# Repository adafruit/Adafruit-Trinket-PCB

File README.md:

## Adafruit Trinket 3.3 and 5V Microcontroller PCBs
&nbsp; 
<br />
Click to purchase from the Adafruit Shop:
- [Adafruit Trinket - Mini Microcontroller - 3.3V Logic - MicroUSB](https://www.adafruit.com/product/1500)
- [Adafruit Trinket - Mini Microcontroller - 5V Logic - MicroUSB](https://www.adafruit.com/product/1501)

Deprecation Warning: The Trinket bit-bang USB technique it uses doesn't work as well as it did in 2014, many modern computers won't work well. So while we still carry the Trinket so that people can maintain some older projects, we no longer recommend it. Please check out the **Trinket M0**. It has built-in USB, more capabilities, and is comparable in price!

Trinket may be small, but do not be fooled by its size! It's a tiny microcontroller board, built around the Atmel ATtiny85, a little chip with a lot of power. We wanted to design a microcontroller board that was small enough to fit into any project, and low cost enough to use without hesitation. Perfect for when you don't want to give up your expensive dev-board and you aren't willing to take apart the project you worked so hard to design. It's our lowest-cost arduino-IDE programmable board!

This is the CAD & PCB data for the Adafruit Trinket 3V & 5V. The PCB format is EagleCAD schematic and board layout
- https://www.adafruit.com/products/1500
- https://www.adafruit.com/products/1501

### License

Adafruit invests time and resources providing this open source design, please support Adafruit and open-source hardware by [purchasing products from Adafruit](https://www.adafruit.com)!

All text above must be included in any redistribution

Designed by Limor Fried/Ladyada for Adafruit Industries.
Creative Commons Attribution/Share-Alike, all text above must be included in any redistribution. 
See license.txt for additional information.

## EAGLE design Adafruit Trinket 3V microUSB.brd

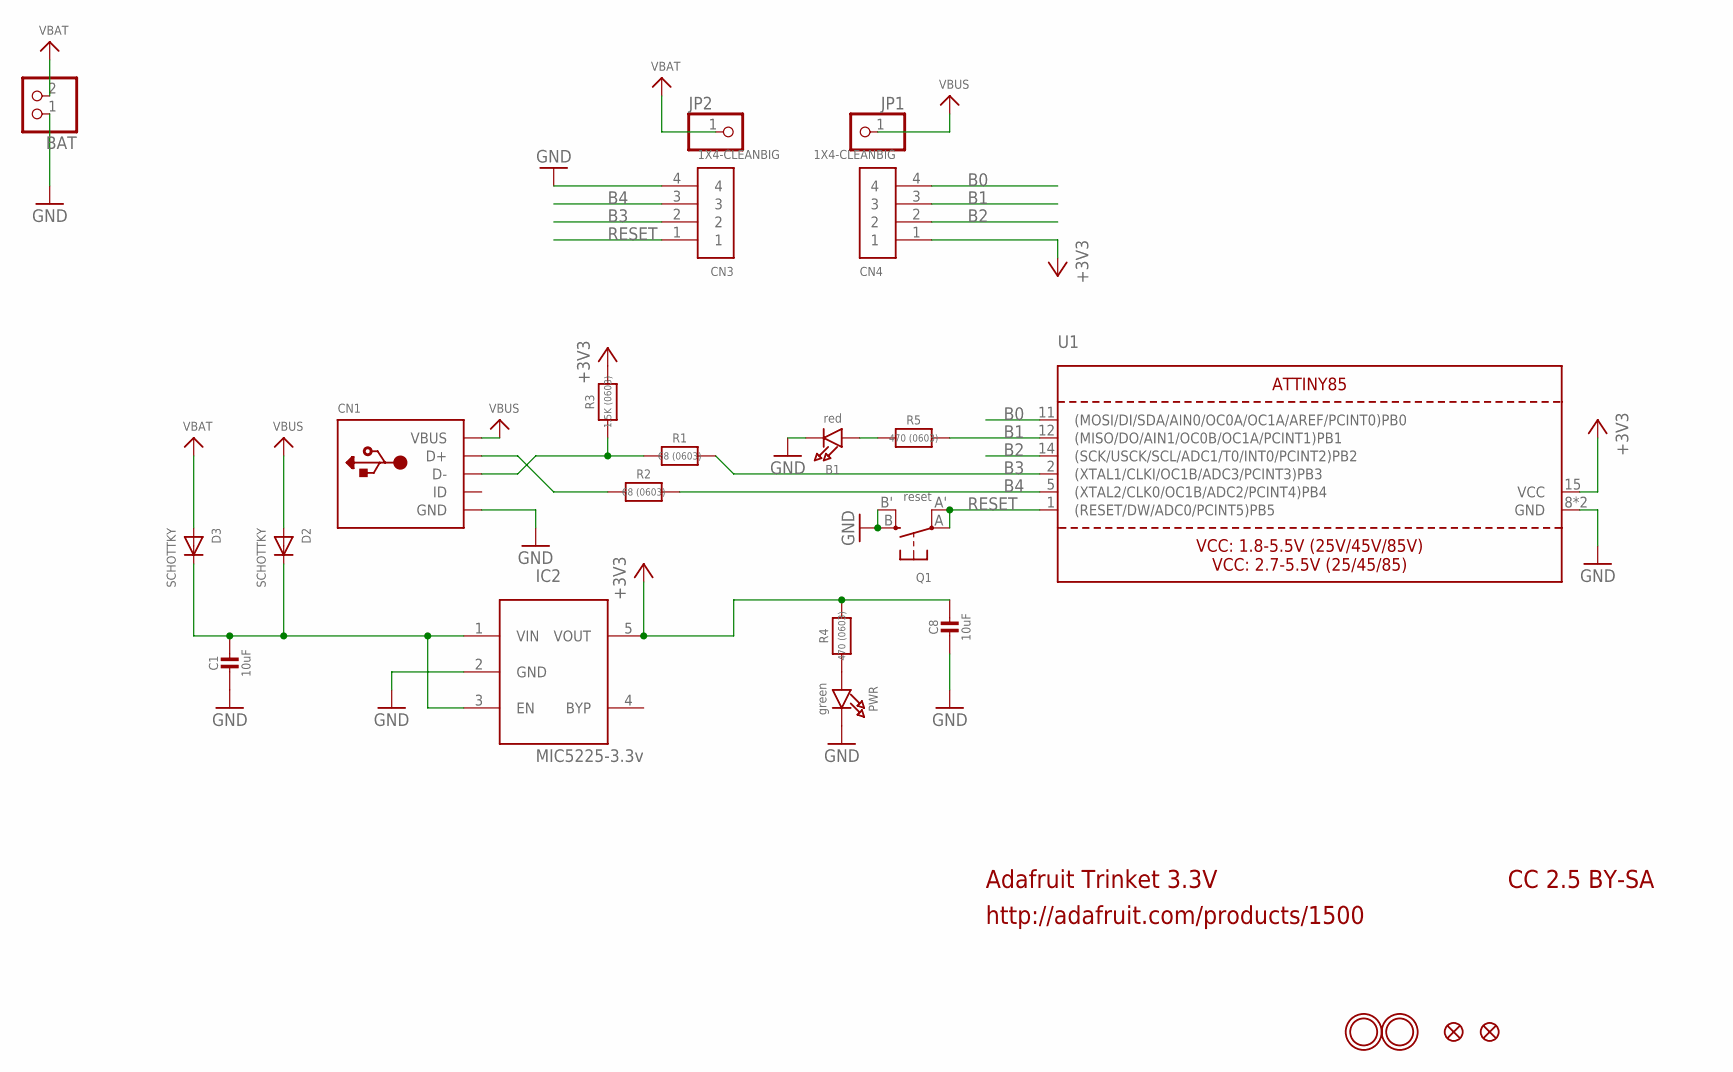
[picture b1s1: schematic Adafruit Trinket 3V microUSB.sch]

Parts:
B1: red; CHIPLED_0805_NOOUTLINE
BAT: CON_JST_PH_2PIN; JSTPH2
C1, C8: 10uF; 0805-NO
CN1: USBMICRO_20329; 4UCONN_20329
CN3, CN4: 1X4-CLEANBIG; 1X04-CLEANBIG
D2, D3: SCHOTTKY; SOD-123FL
IC2: MIC5225-3.3v; SOT23-5L
JP1, JP2: PINHD-1X1CB; 1X01-CLEANBIG
PWR: green; CHIPLED_0805_NOOUTLINE
Q1: reset; BTN_KMR2_4.6X2.8
R1, R2: 68 (0603); 0603-NO
R3: 1.5K (0603); 0603-NO
R4, R5: 470 (0603); 0603-NO
U1: ATTINY85; MLF20_4X4MM_0.5MM_ATMEL
U$1, U$6: FIDUCIAL""; FIDUCIAL_1MM
U$8, U$9: MOUNTINGHOLE2.0; MOUNTINGHOLE_2.0_PLATED

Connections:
+3V3: C8.1, CN4.1, IC2.5 (VOUT), R3.2, R4.2, U1.15 (VCC)
B0: CN4.4, U1.11 ((MOSI/DI/SDA/AIN0/OC0A/OC1A/AREF/PCINT0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)
B1: CN4.3, R5.2, U1.12 ((MISO/DO/AIN1/OC0B/OC1A/PCINT1)PB1)
B2: CN4.2, U1.14 ((SCK/USCK/SCL/ADC1/T0/INT0/PCINT2)PB2)
B3: CN3.2, R1.2, U1.2 ((XTAL1/CLKI/OC1B/ADC3/PCINT3)PB3)
B4: CN3.3, R2.2, U1.5 ((XTAL2/CLK0/OC1B/ADC2/PCINT4)PB4)
D+: CN1.D+, R2.1
D-: CN1.D-, R1.1, R3.1
GND: B1.C, BAT.1, C1.2, C8.2, CN1.BASE@1 (GND), CN1.BASE@2 (GND), CN1.GND, CN1.SPRT@1 (GND), CN1.SPRT@2 (GND), CN1.SPRT@3 (GND), CN1.SPRT@4 (GND), CN3.4, IC2.2 (GND), PWR.C, Q1.B (S), Q1.B' (S1), U1.8 (GND), U1.THERMAL (GND)
unnamed: B1.A, R5.1
unnamed: PWR.A, R4.1
unnamed: C1.1, D2.C, D3.C, IC2.1 (VIN), IC2.3 (EN)
RESET: CN3.1, Q1.A, Q1.A' (P1), U1.1 ((RESET/DW/ADC0/PCINT5)PB5)
VBAT: BAT.2, D3.A, JP2.1
VBUS: CN1.VBUS, D2.A, JP1.1

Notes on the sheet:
Adafruit Trinket 3.3V
http://adafruit.com/products/1500
CC 2.5 BY-SA

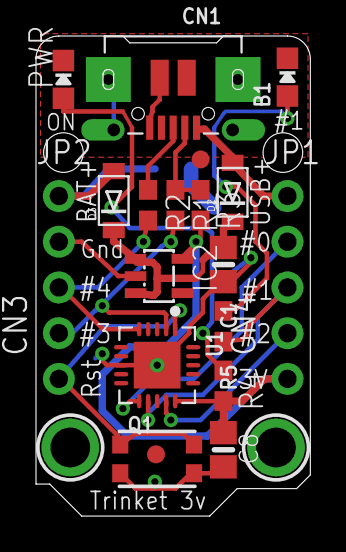
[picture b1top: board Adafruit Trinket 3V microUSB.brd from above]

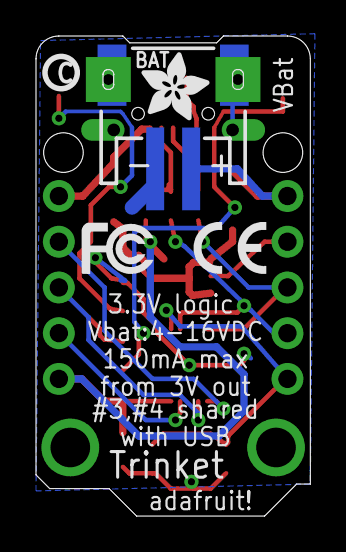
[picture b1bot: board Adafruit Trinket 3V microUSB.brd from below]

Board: 2 copper layers, 15.2 x 26.7 mm, 28 parts (5 on the bottom side), 15 nets.

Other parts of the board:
U$5: ADAFRUIT_3.5MM
U$12: PCBFEAT-REV-040
U$13: SYMBOL_FCC_TINY
U$14: SYMBOL_CE_TINY

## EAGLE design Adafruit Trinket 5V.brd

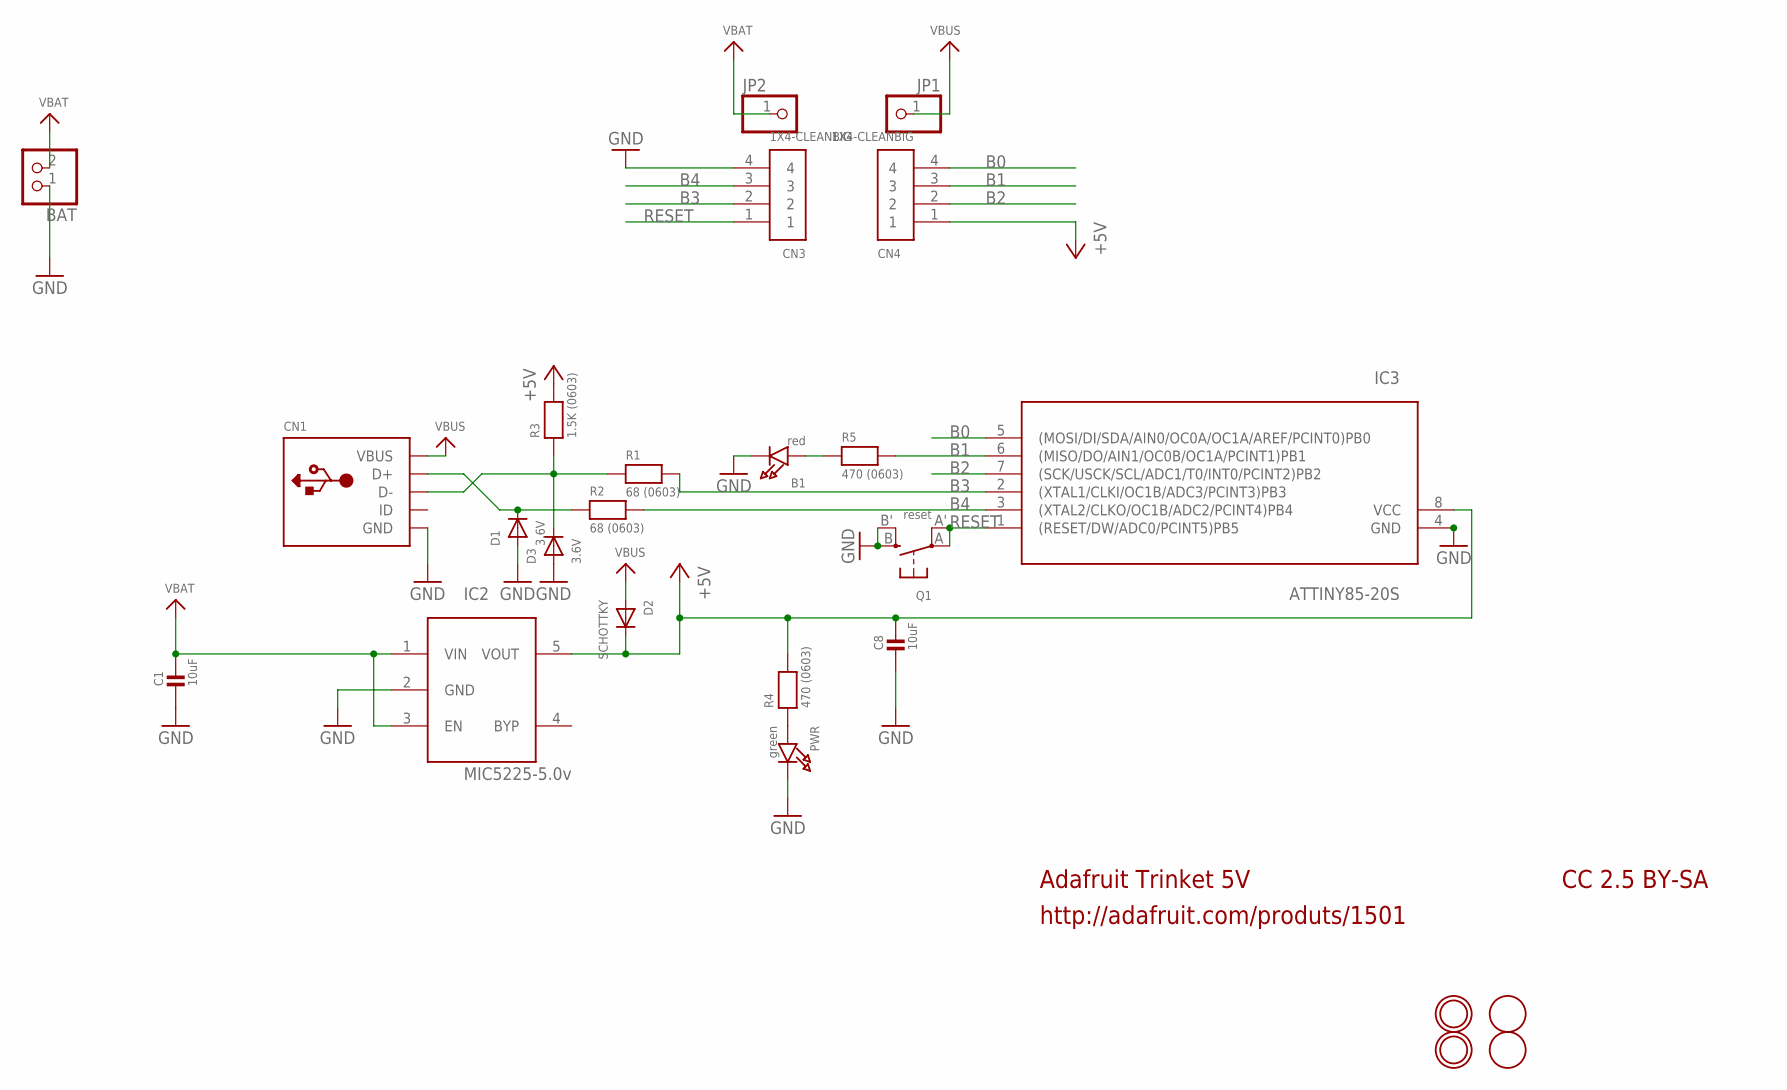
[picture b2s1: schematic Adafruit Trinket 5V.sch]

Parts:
B1: red; CHIPLED_0805_NOOUTLINE
BAT: CON_JST_PH_2PIN; JSTPH2
C1, C8: 10uF; 0805-NO
CN1: USBMINIB; USB-MINIB
CN3, CN4: 1X4-CLEANBIG; 1X04-CLEANBIG
D1, D3: 3.6V; SOD-323
D2: SCHOTTKY; SOD-123FL
IC2: MIC5225-5.0v; SOT23-5L
IC3: ATTINY85-20S; SOIC8
JP1, JP2: PINHD-1X1CB; 1X01-CLEANBIG
PWR: green; CHIPLED_0805_NOOUTLINE
Q1: reset; BTN_KMR2_4.6X2.8
R1, R2: 68 (0603); 0603-NO
R3: 1.5K (0603); 0603-NO
R4, R5: 470 (0603); 0603-NO
U$1, U$6: FIDUCIAL; FIDUCIAL_1MM
U$8, U$9: MOUNTINGHOLE2.0; MOUNTINGHOLE_2.0_PLATED

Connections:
+5V: C8.1, CN4.1, D2.C, IC2.5 (VOUT), IC3.8 (VCC), R3.2, R4.2
B0: CN4.4, IC3.5 ((MOSI/DI/SDA/AIN0/OC0A/OC1A/AREF/PCINT0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)
B1: CN4.3, IC3.6 ((MISO/DO/AIN1/OC0B/OC1A/PCINT1)PB1), R5.2
B2: CN4.2, IC3.7 ((SCK/USCK/SCL/ADC1/T0/INT0/PCINT2)PB2)
B3: CN3.2, IC3.2 ((XTAL1/CLKI/OC1B/ADC3/PCINT3)PB3), R1.2
B4: CN3.3, IC3.3 ((XTAL2/CLKO/OC1B/ADC2/PCINT4)PB4), R2.2
GND: B1.C, BAT.1, C1.2, C8.2, CN1.GND, CN1.GND1 (GND), CN1.GND2 (GND), CN1.GND3 (GND), CN1.GND4 (GND), CN3.4, D1.A, D3.A, IC2.2 (GND), IC3.4 (GND), PWR.C, Q1.B (S), Q1.B' (S1)
unnamed: B1.A, R5.1
unnamed: CN1.D+, D1.C, R2.1
unnamed: CN1.D-, D3.C, R1.1, R3.1
unnamed: PWR.A, R4.1
RESET: CN3.1, IC3.1 ((RESET/DW/ADC0/PCINT5)PB5), Q1.A, Q1.A' (P1)
VBAT: BAT.2, C1.1, IC2.1 (VIN), IC2.3 (EN), JP2.1
VBUS: CN1.VBUS, D2.A, JP1.1

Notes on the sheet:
Adafruit Trinket 5V
http://adafruit.com/produts/1501
CC 2.5 BY-SA

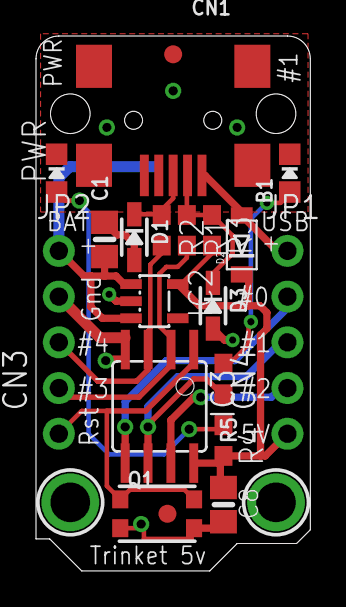
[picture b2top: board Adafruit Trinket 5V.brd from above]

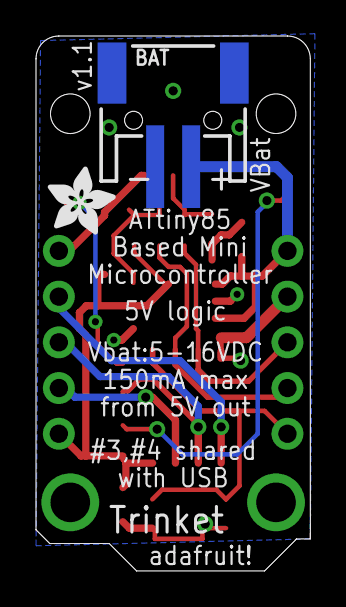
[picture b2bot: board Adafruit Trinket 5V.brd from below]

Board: 2 copper layers, 15.2 x 29.7 mm, 26 parts (2 on the bottom side), 14 nets.

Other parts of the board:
U$5: ADAFRUIT_3.5MM

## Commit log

2014-04-14 whee!
2014-04-14 urlz
2016-01-17 with microUSB connectors
2021-11-19 Added prettypins pdfs

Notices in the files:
parts and their libraries:
microbuilder: This work is placed in the public domain, and may be freely used for commercial and non-commercial work with the following conditions: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
